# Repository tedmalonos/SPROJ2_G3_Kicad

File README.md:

Semester Project 2 - Group 3 - Phobiameter  
KiCAD PCB files

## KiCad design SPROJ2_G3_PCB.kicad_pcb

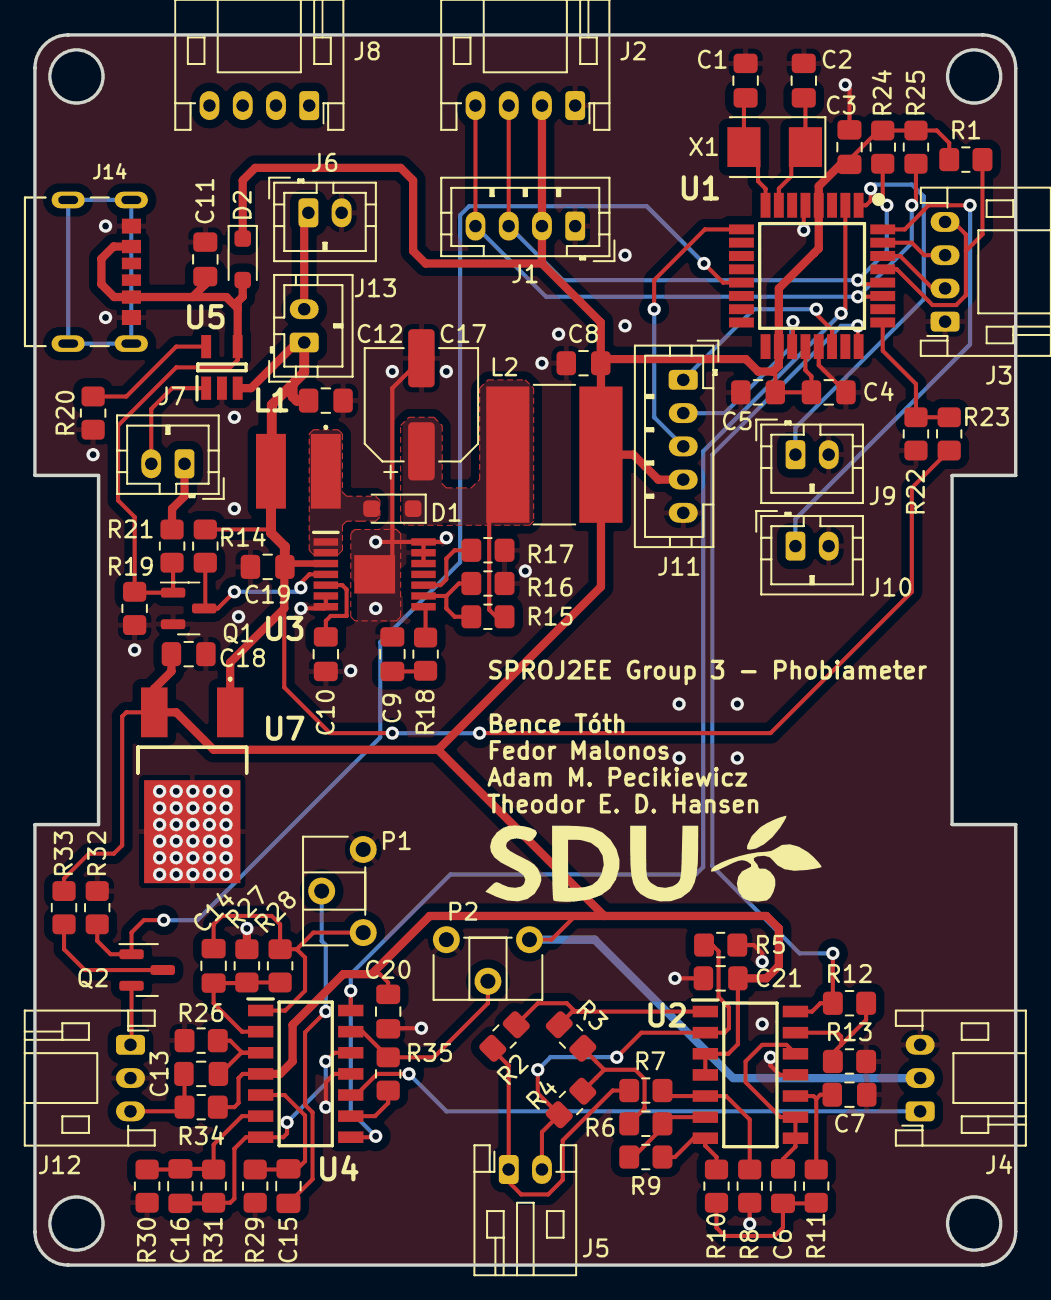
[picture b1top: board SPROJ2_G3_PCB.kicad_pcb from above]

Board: 2 copper layers, 59.0 x 74.0 mm, 85 parts (0 on the bottom side), 57 nets.

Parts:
C1, C2: 10p; C_0805_2012Metric_Pad1.18x1.45mm_HandSolder
C3, C4, C5, C13, C14, C15, C16, C20, C21: 100n; C_0805_2012Metric_Pad1.18x1.45mm_HandSolder
C6, C7, C8, C9, C10, C18: C; C_0805_2012Metric_Pad1.18x1.45mm_HandSolder
C11, C12, C19: 4.7u; C_0805_2012Metric_Pad1.18x1.45mm_HandSolder
C17: 100n; CP_Elec_6.3x5.4
D1, D2: D; D_SOD-323_HandSoldering
J1: Conn_01x04_Pin; JST_PH_B4B-PH-K_1x04_P2.00mm_Vertical
J2, J3, J8: Conn_01x04_Pin; JST_PH_S4B-PH-K_1x04_P2.00mm_Horizontal
J4, J12: Conn_01x03_Pin; JST_PH_S3B-PH-K_1x03_P2.00mm_Horizontal
J5: Conn_01x02_Pin; JST_PH_S2B-PH-K_1x02_P2.00mm_Horizontal
J6, J7, J9, J10, J13: Conn_01x02_Pin; JST_PH_B2B-PH-K_1x02_P2.00mm_Vertical
J11: Conn_01x05_Pin; JST_PH_B5B-PH-K_1x05_P2.00mm_Vertical
J14: UJC-HP-3-SMT-TR; CUI_UJC-HP-3-SMT-TR
L1: SDR0403-5R6ML; SDR04035R6ML
L2: L; L_Bourns-SRN8040_8x8.15mm
P1, P2: R_Potentiometer; Potentiometer_ACP_CA6-H2,5_Horizontal
Q1: Q_NMOS_GSD; SOT-23
Q2: Q_PMOS_GSD; SOT-23
R1, R22, R23: 10k; R_0805_2012Metric_Pad1.20x1.40mm_HandSolder
R2, R3, R4, R5, R6, R7, R8, R9, R10, R11, R12, R13, R14, R15, R16, R17, R18, R19, R20, R21, R24, R25, R26, R27, R28, R29, R30, R31, R32, R33, R34: R; R_0805_2012Metric_Pad1.20x1.40mm_HandSolder
R35: 0R; R_0805_2012Metric_Pad1.20x1.40mm_HandSolder
U1: ATMEGA328PB-AU; QFP80P900X900X120-32N
U2, U4: LMV324BG-13; SOIC127P600X173-14N
U3: TPS61175PWPR; SOP65P640X120-15N
U5: MCP73831T-2ACI_OT; SOT95P270X145-5N
U7: MC7805CDTG
X1: Crystal; Crystal_SMD_5032-2Pin_5.0x3.2mm

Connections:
+5V: C3.1, C4.1, C5.1, C8.1, C18.1, C20.1, C21.1, D2.1 (K), J1.2, J2.2, J4.2, J11.4, L2.2, P2.1, R1.2, R24.1, R25.2, R33.2, R34.2, U1.4 (VCC), U1.18 (AVCC), U1.20 (AREF), U2.3 (INA+), U2.4 (V+), U4.4 (V+), U7.3 (OUTPUT)
+BATT: C12.1, C19.1, J13.1, L1.2, R14.2, R23.2, U3.3 (VIN), U5.3 (VBAT), U7.1 (INPUT)
/Feedback: R15.1, R16.2, U3.9 (FB)
/SW_1: D1.2 (A), L1.1, U3.1 (SW_1), U3.2 (SW_2)
/XTAL1: C2.1, U1.7 ((XTAL1/TOSC1)_PB6), X1.1
/XTAL2: C1.1, U1.8 ((XTAL2/TOSC2)_PB7), X1.2
A1: R12.2, U1.24 (PC1_(ADC1/PTCY/SCK1)), U2.14 (OUTD)
ADC6: J11.2, U1.19 (PE2_(ADC6/PTCY/ICP3/~SS1))
ADC7: J11.1, U1.22 (PE3_(ADC7/PTCY/T3/MOSI1))
GND: C1.2, C2.2, C3.2, C4.2, C5.2, C7.2, C8.2, C9.2, C10.2, C11.2, C12.2, C17.2, C18.2, C19.2, C20.2, C21.2, J1.1, J2.1, J3.1, J4.3, J6.2, J9.2, J10.2, J11.5, J12.2, J14.A12 (GND), J14.B12 (GND), P1.3, P2.3, Q1.2 (S), R5.2, R8.1, R13.1, R16.1, R17.1, R19.1, R20.1, R22.1, R26.1, R27.1, R29.1, R30.1, R32.1, U1.5 (GND_1), U1.21 (GND_2), U2.11 (V-), U3.6 (SYNC), U3.7 (AGND), U3.12 (PGND_1), U3.13 (PGND_2), U3.14 (PGND_3), U3.15 (EP), U4.11 (V-), U5.2 (VSS), U7.2 (GROUND)
INV_A: J5.2, R4.2, R5.1, U2.2 (INA-)
INV_A_1: C14.1, R27.2, R28.2, U4.2 (INA-)
INV_B: R6.2, R9.1, U2.6 (INB-)
INV_B_1: C16.1, R30.2, R31.2, U4.6 (INB-)
INV_C: C6.1, U2.8 (OUTC), U2.9 (INC-), U2.12 (IND+)
INV_C_1: R35.1, U4.9 (INC-)
INV_D: R12.1, R13.2, U2.13 (IND-)
INV_D_1: P2.2, R35.2, U4.13 (IND-)
unnamed: C6.2, R10.2, R11.1
unnamed: C9.1, R18.1
unnamed: C15.1, P1.2
unnamed: C17.1, D1.1 (K), L2.1, R15.2
unnamed: J5.1, R2.2, R7.1
unnamed: J7.1, R21.1
unnamed: J7.2, U5.1 (STAT)
unnamed: J12.1, Q2.2 (S)
unnamed: C13.1, J12.3, R34.1
unnamed: J6.1, J13.2
unnamed: J14.S1 (SHIELD), J14.S2 (SHIELD), J14.S3 (SHIELD), J14.S4 (SHIELD)
unnamed: Q1.3 (D), R14.1, U3.4 (EN)
unnamed: Q2.3 (D), R33.1
unnamed: R3.2, R4.1, R6.1
unnamed: R22.2, R23.1, U1.25 (PC2_(ADC2/PTCY))
unnamed: R18.2, U3.8 (COMP)
unnamed: R17.2, U3.10 (FREQ)
unnamed: C10.1, U3.5 (SS)
unnamed: R20.2, U5.5 (PROG)
Non_INV_A_1: C13.2, R26.2, U4.3 (INA+)
Non_INV_B: R7.2, R8.2, U2.5 (INB+)
Non_INV_B_1: C15.2, R29.2, U4.5 (INB+)
Non_INV_C: C7.1, R11.2, U2.10 (INC+)
Non_INV_C_1: J4.1, U4.10 (INC+)
Non_INV_D_1: C16.2, R31.1, U4.7 (OUTB), U4.12 (IND+)
Out_A: R2.1, R3.1, U2.1 (OUTA)
Out_A_1: C14.2, P1.1, R28.1, U4.1 (OUTA)
Out_B: R9.2, R10.1, U2.7 (OUTB)
Out_C_1: U1.2 ((XCK0/T0/PTCXY)_PD4), U4.8 (OUTC), U4.14 (OUTD)
PD2: J10.1, U1.32 (PD2_(PTCXY/INT0/OC3B/OC4B))
PD3: J9.1, U1.1 ((OC2B/INT1/PTCXY)_PD3)
PD5: J11.3, U1.9 ((OC0B/T1/PTCXY)_PD5)
PI_EN: Q2.1 (G), R32.2, U1.13 ((OC1A/PTCXY)_PB1)
RX: J3.2, U1.30 (PD0_(PTCXY/OC3A/RXD0))
SCL: J1.3, J2.3, R24.2, U1.28 (PC5_(ADC5/PTCY/SCL0))
SDA: J1.4, J2.4, R25.1, U1.27 (PC4_(ADC4/PTCY/SDA0))
TX: J3.3, U1.31 (PD1_(PTCXY/OC4A/TXD0))
VBUS: C11.1, D2.2 (A), J14.A9 (V-BUS), J14.B9 (V-BUS), Q1.1 (G), R19.2, R21.2, U5.4 (VDD)
~RESET: J3.4, R1.1, U1.29 (PC6_(~RESET))

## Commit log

2024-05-28 Create README.md
    Create README.md
2024-05-28 Final PCB files upload
    Final PCB files upload
2024-05-28 Schematic
    Schematic
2024-05-29 New schematic
    New schematic
2024-06-02 Final schematic
    Final schematic
2024-06-02 Final sch
    Final sch
